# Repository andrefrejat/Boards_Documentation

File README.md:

# Boards_Documentation
General boards for many different purposes

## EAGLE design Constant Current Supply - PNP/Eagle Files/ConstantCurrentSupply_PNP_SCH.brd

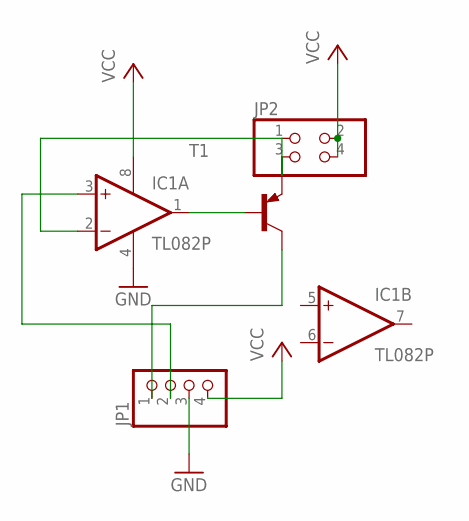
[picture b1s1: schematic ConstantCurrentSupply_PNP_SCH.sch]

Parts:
IC1: TL082P; DIL08
JP1: PINHD-1X4; 1X04
JP2: PINHD-2X2; 2X02
T1: 2N3906-PNP-TO92-EBC; TO92-EBC

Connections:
COLLECTOR: JP1.1, T1.C
GND: IC1.4 (V-), JP1.3
OUT: IC1.1 (OUT), T1.B
V+: IC1.3 (+IN), JP1.2
V-: IC1.2 (-IN), JP2.1, JP2.3, T1.E
VCC: IC1.8 (V+), JP1.4, JP2.2, JP2.4

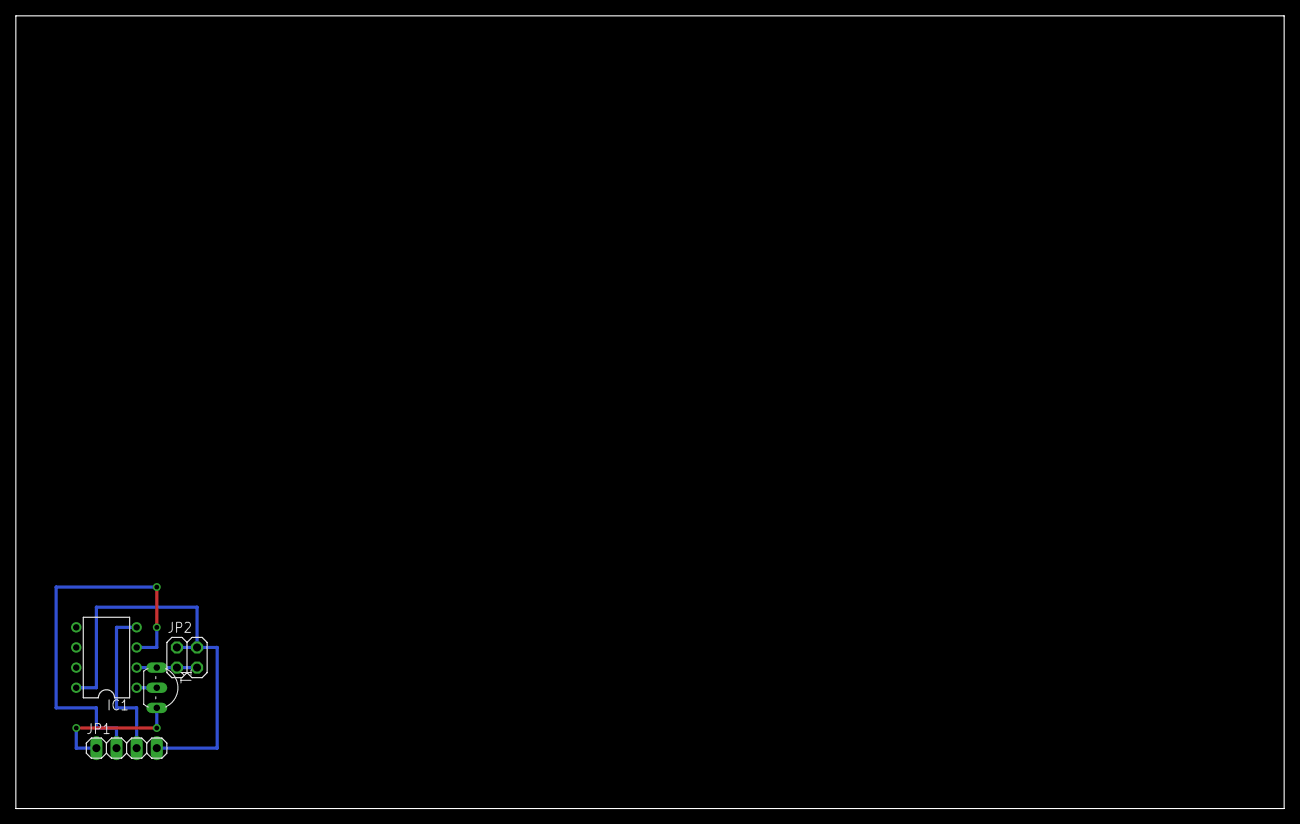
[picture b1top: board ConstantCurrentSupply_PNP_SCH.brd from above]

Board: 2 copper layers, 160.0 x 100.0 mm, 4 parts (0 on the bottom side), 6 nets.

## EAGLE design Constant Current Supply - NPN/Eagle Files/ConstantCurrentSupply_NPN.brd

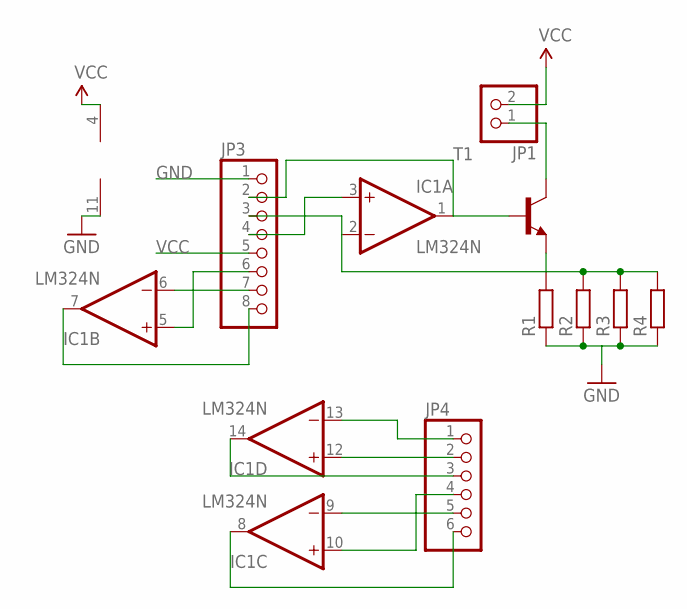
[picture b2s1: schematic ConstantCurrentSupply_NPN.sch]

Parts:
IC1: LM324N; DIL14
JP1: PINHD-1X2; 1X02
JP3: PINHD-1X8; 1X08
JP4: PINHD-1X6; 1X06
R1, R2, R3, R4: R-EU_0204/2V; 0204V
T1: 2N3904-NPN-TO92-EBC; TO92-EBC

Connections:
GND: IC1.11 (V-), JP3.1, R1.1, R2.1, R3.1, R4.1
unnamed: IC1.2 (-IN), JP3.3, R1.2, R2.2, R3.2, R4.2, T1.E
unnamed: IC1.1 (OUT), JP3.2, T1.B
unnamed: JP1.1, T1.C
unnamed: IC1.3 (+IN), JP3.4
unnamed: IC1.5 (+IN), JP3.6
unnamed: IC1.6 (-IN), JP3.7
unnamed: IC1.7 (OUT), JP3.8
unnamed: IC1.10 (+IN), JP4.4
unnamed: IC1.13 (-IN), JP4.1
unnamed: IC1.12 (+IN), JP4.2
unnamed: IC1.14 (OUT), JP4.3
unnamed: IC1.9 (-IN), JP4.5
unnamed: IC1.8 (OUT), JP4.6
VCC: IC1.4 (V+), JP1.2, JP3.5

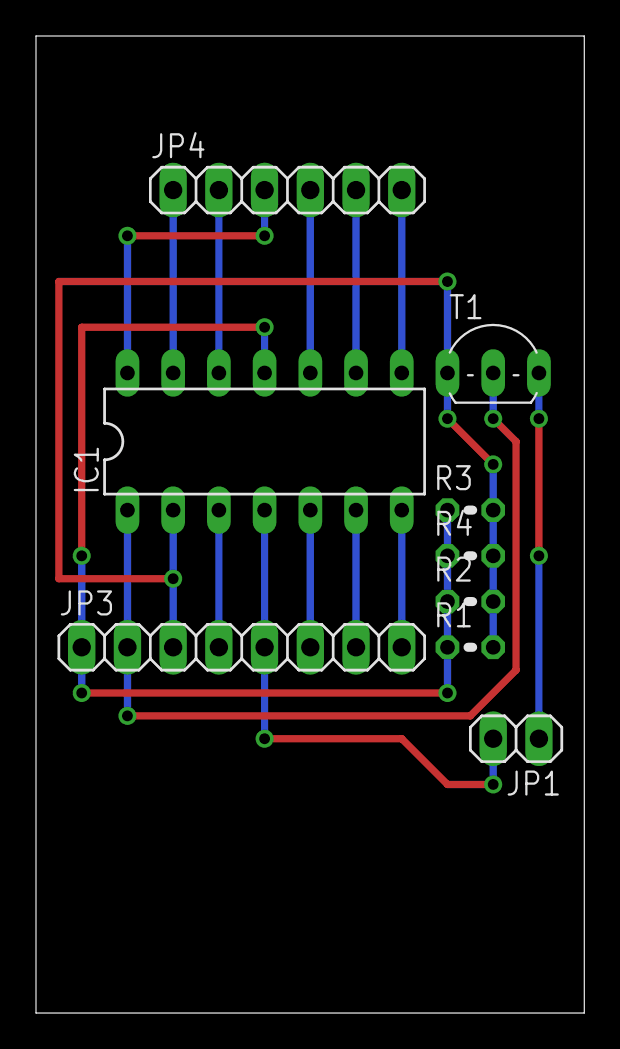
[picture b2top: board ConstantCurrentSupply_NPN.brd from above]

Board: 2 copper layers, 30.5 x 54.3 mm, 9 parts (0 on the bottom side), 15 nets.

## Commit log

2016-11-11 Upladed boards, pictures and schematics
2016-11-11 Reorganized
